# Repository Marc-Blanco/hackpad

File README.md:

# hackpad
Is a really simple hackpad followed by the hackclub tutorial
-----------------------------------------------------------------------
## Firmware
https://docs.qmk.fm/newbs_building_firmware_configurator
## Images

his is a broad representation it actually fits well

## BOM

| Part | Quantity | link |
| ---- | ------| -----|
| Keys | x6 | splitkb.com |
| Body | x2 |-----|
| Pcb | x5 | pcbway.com |
|speaker| x1 | already have|
| xiao | x1 | Aliexpress.com|
| leds | x2 | Aliexpress.com|

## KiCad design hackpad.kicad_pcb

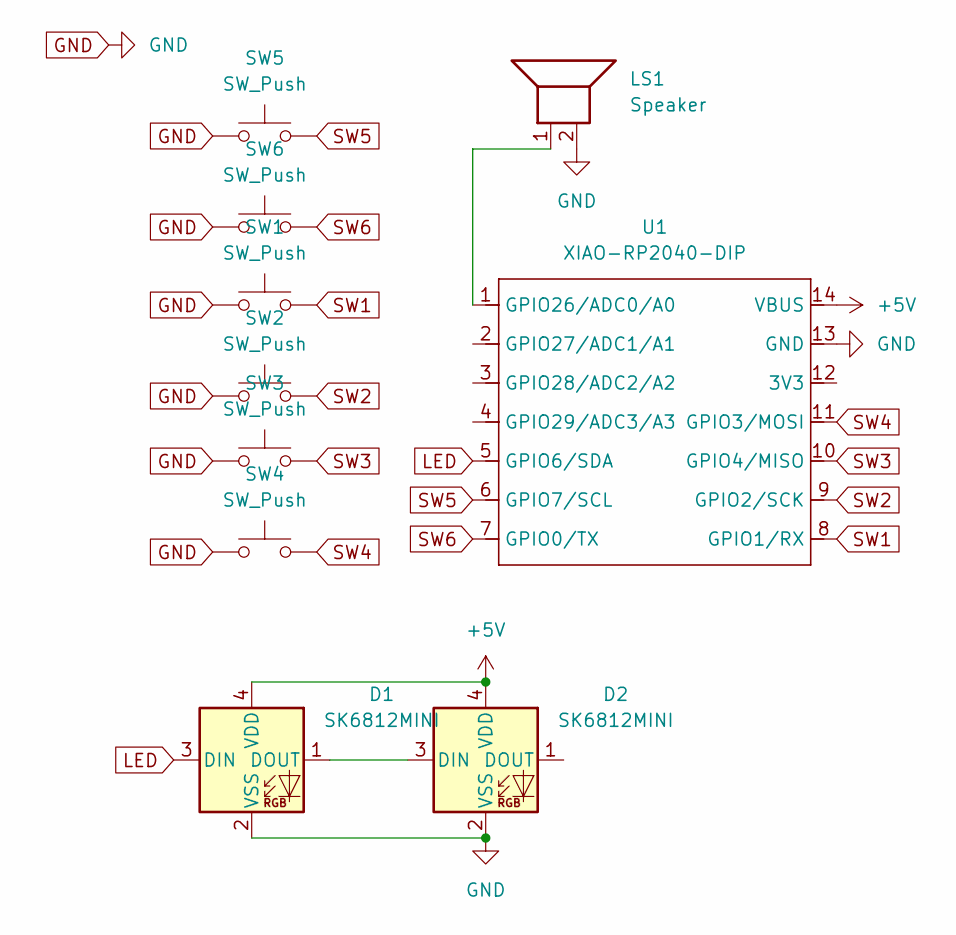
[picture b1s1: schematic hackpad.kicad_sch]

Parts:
D1, D2: SK6812MINI; LED_SK6812MINI_PLCC4_3.5x3.5mm_P1.75mm
LS1: Speaker; Speaker_CUI_CMR-1206S-67
SW1, SW2, SW3, SW4, SW5, SW6: SW_Push; SW_Cherry_MX_1.00u_PCB
U1: XIAO-RP2040-DIP

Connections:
+5V: D1.4 (VDD), D2.4 (VDD), U1.14 (VBUS)
GND: D1.2 (VSS), D2.2 (VSS), LS1.2, SW1.1, SW2.1, SW3.1, SW4.1, SW5.1, SW6.1, U1.13 (GND)
LED: D1.3 (DIN), U1.5 (GPIO6/SDA)
unnamed: D1.1 (DOUT), D2.3 (DIN)
unnamed: LS1.1, U1.1 (GPIO26/ADC0/A0)
SW1: SW1.2, U1.8 (GPIO1/RX)
SW2: SW2.2, U1.9 (GPIO2/SCK)
SW3: SW3.2, U1.10 (GPIO4/MISO)
SW4: SW4.2, U1.11 (GPIO3/MOSI)
SW5: SW5.2, U1.6 (GPIO7/SCL)
SW6: SW6.2, U1.7 (GPIO0/TX)

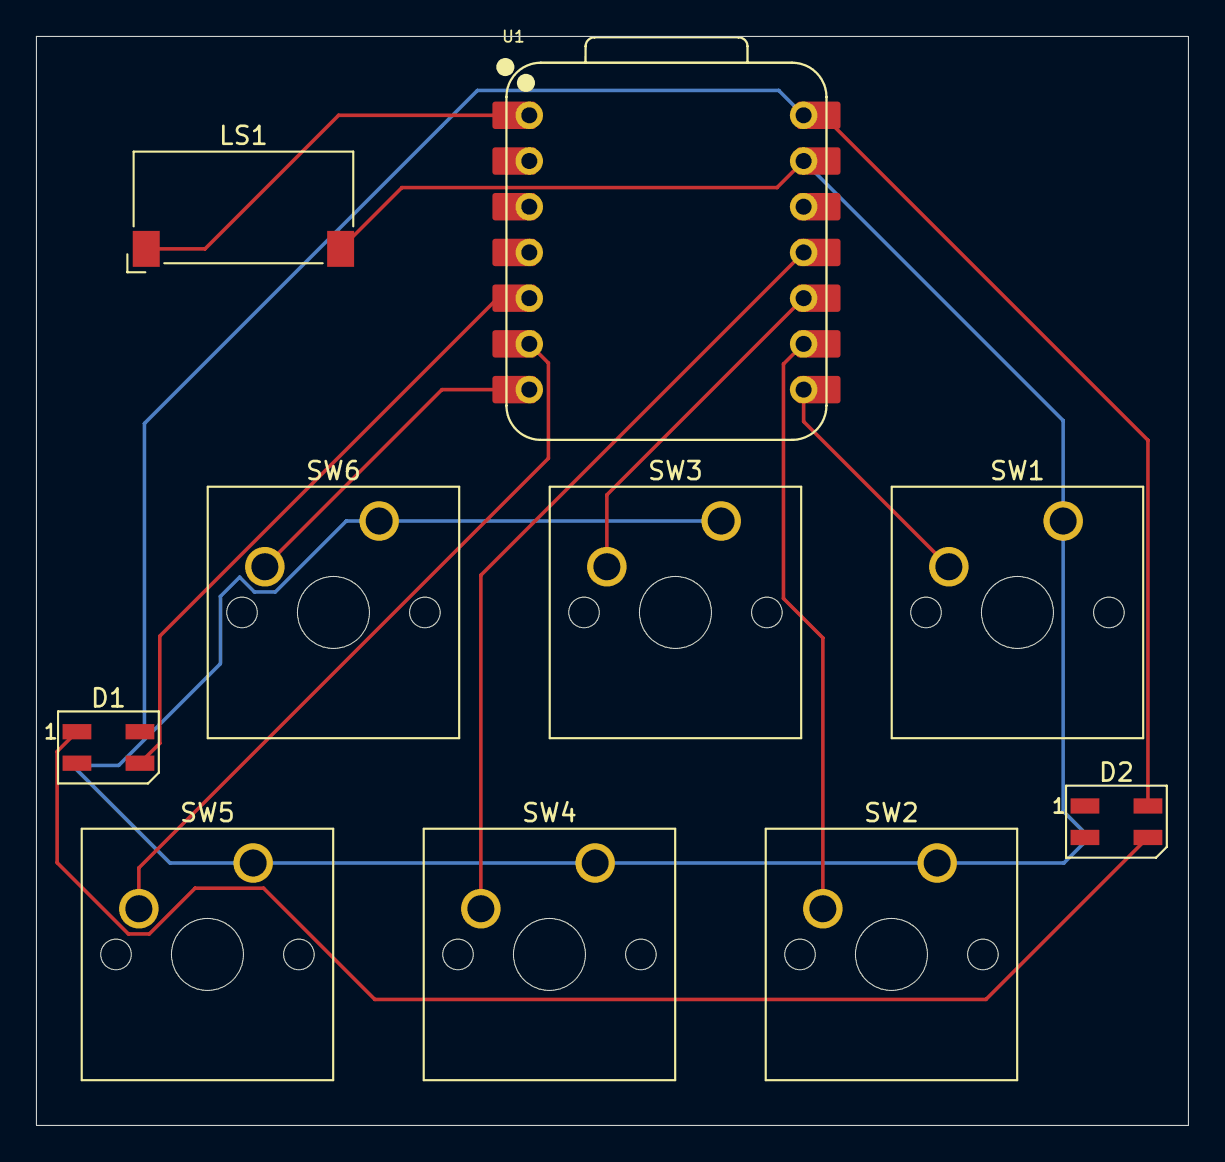
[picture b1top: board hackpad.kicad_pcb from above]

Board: 2 copper layers, 64.0 x 60.5 mm, 10 parts (0 on the bottom side), 11 nets.

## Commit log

2025-07-13 Create a
2025-07-13 Rename gerber.zip to CAD/gerber.zip
2025-07-13 Rename pad.FCStd to CAD/pad.FCStd
2025-07-13 Rename toppad.step to CAD/toppad.step
2025-09-13 Add BOM section to README
    Added BOM section with parts and quantities.
